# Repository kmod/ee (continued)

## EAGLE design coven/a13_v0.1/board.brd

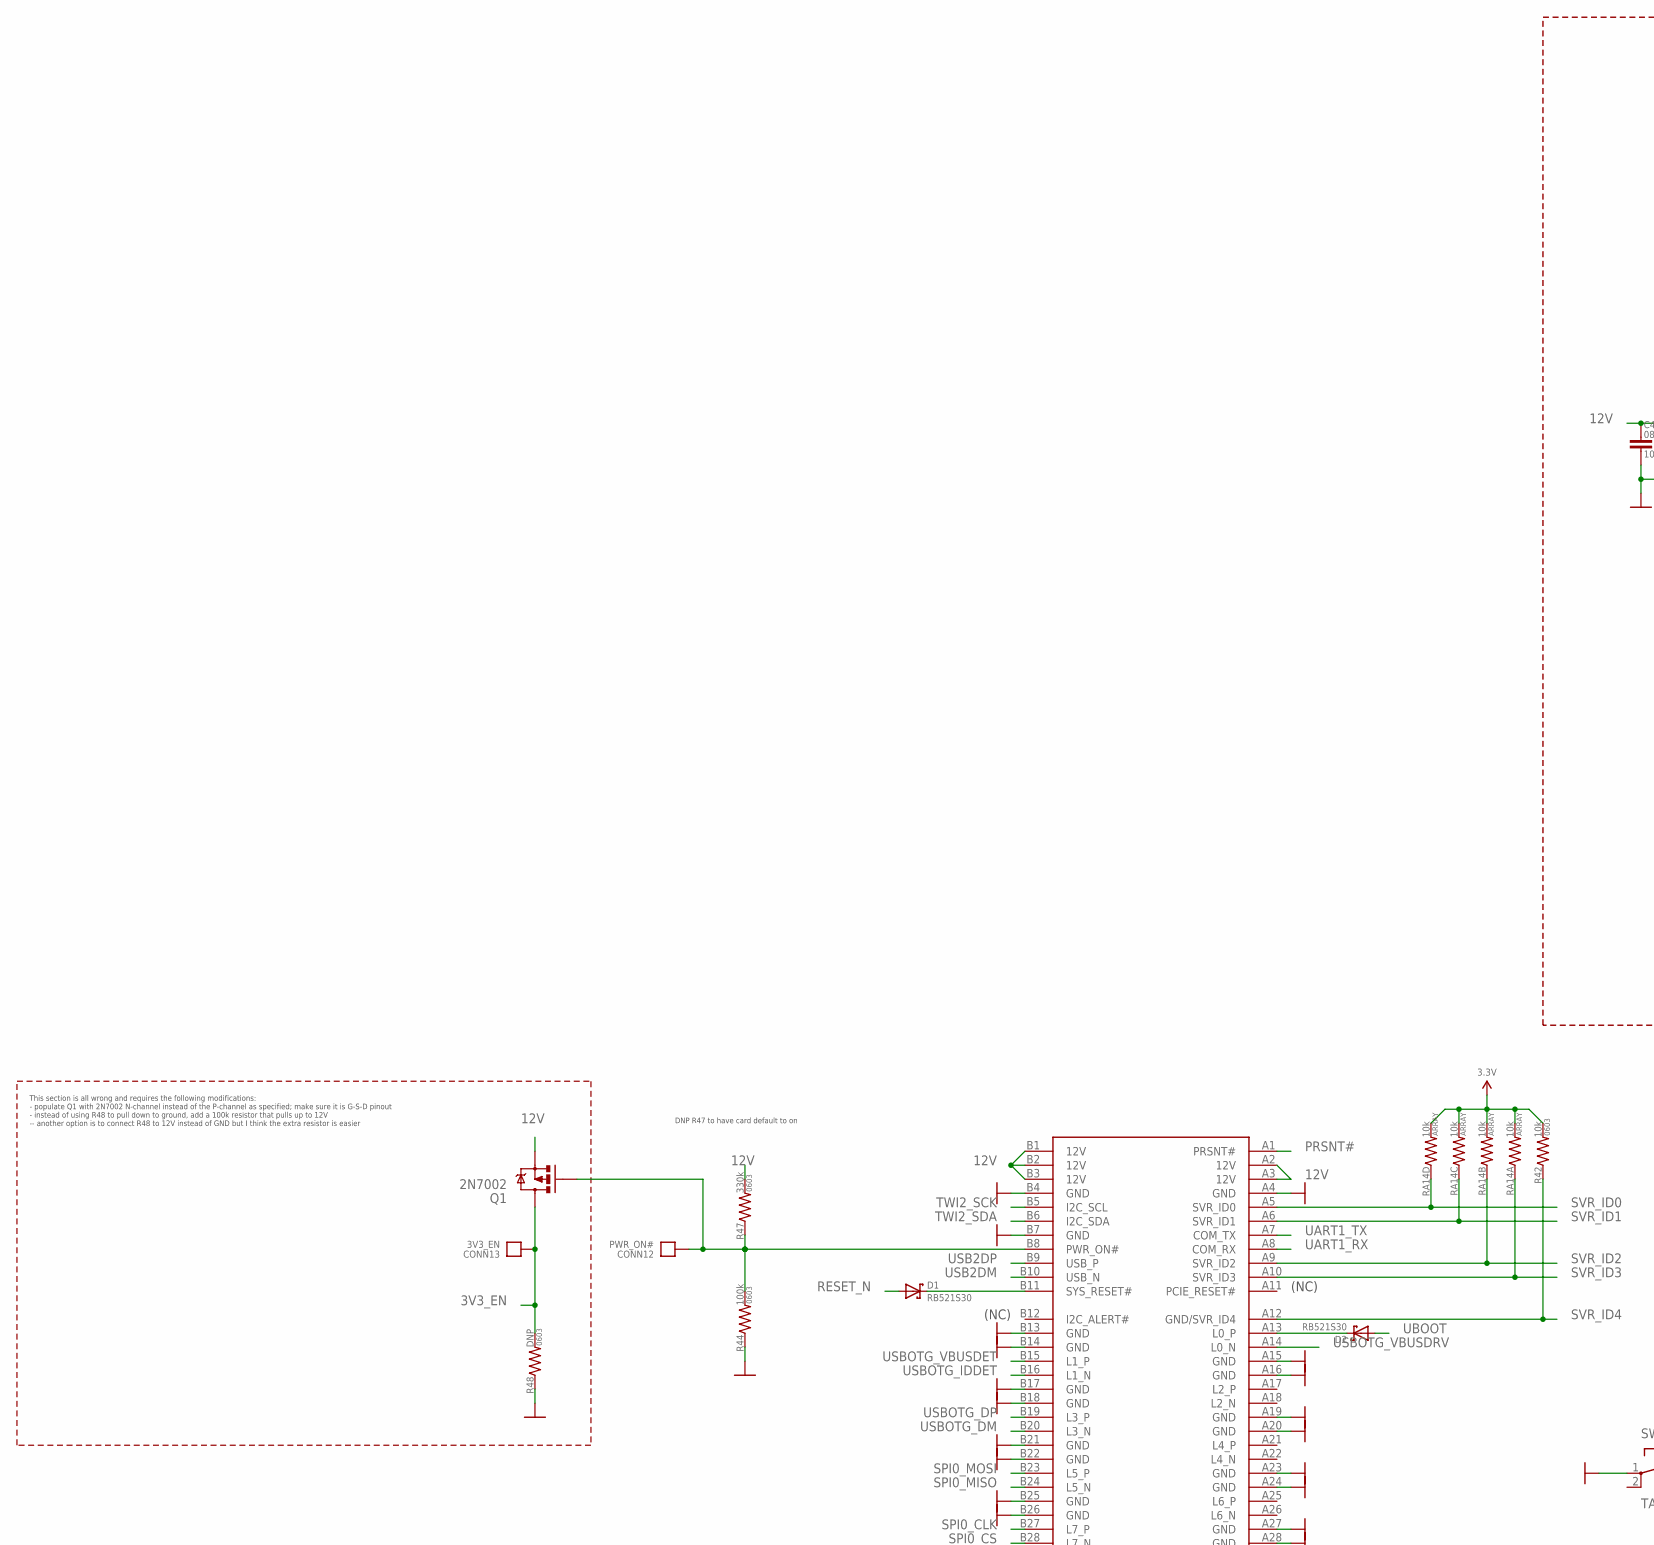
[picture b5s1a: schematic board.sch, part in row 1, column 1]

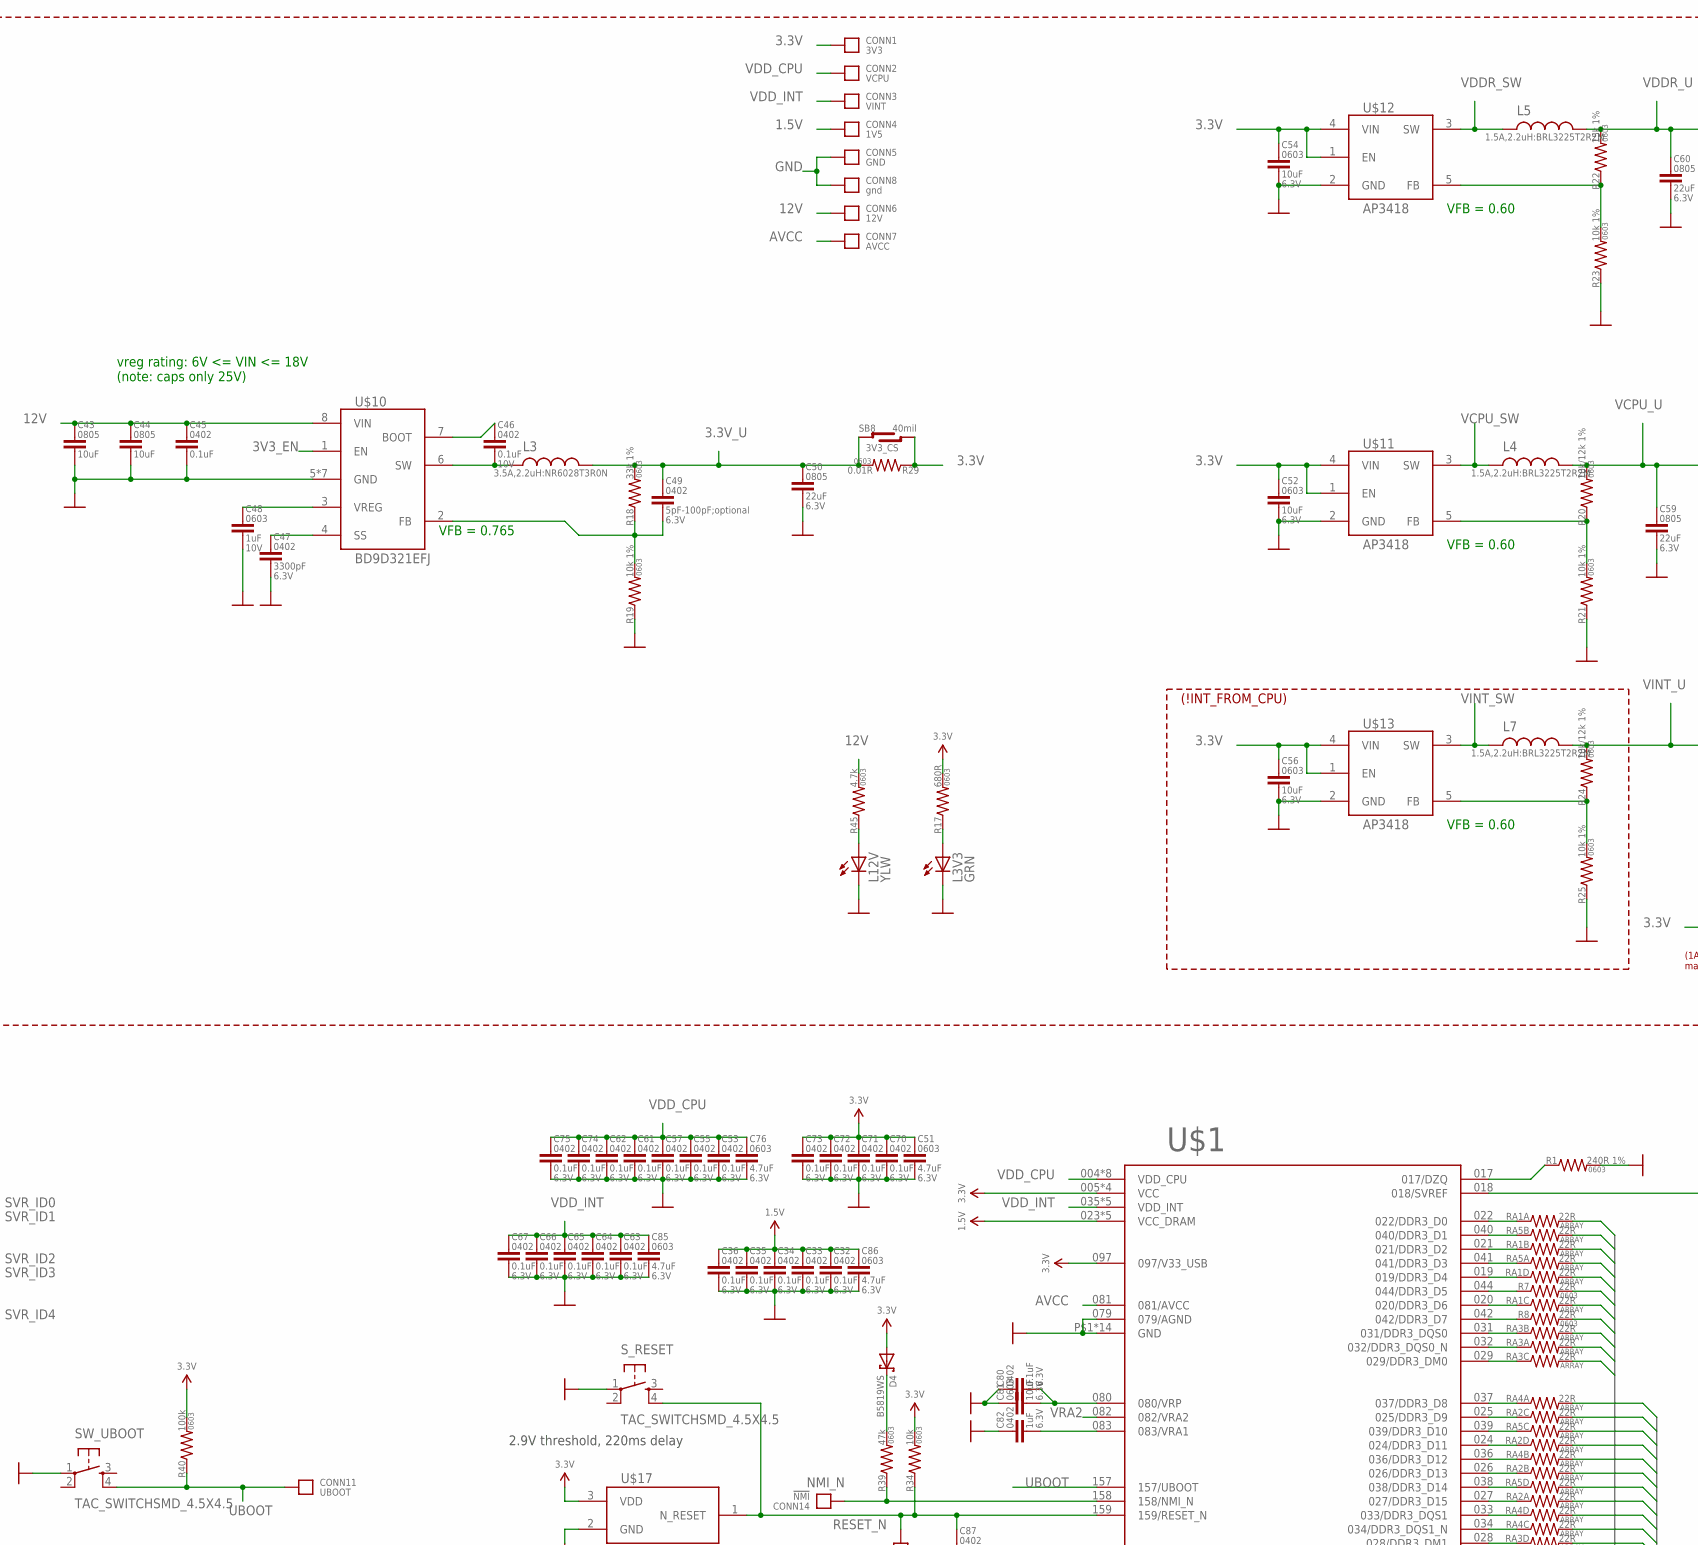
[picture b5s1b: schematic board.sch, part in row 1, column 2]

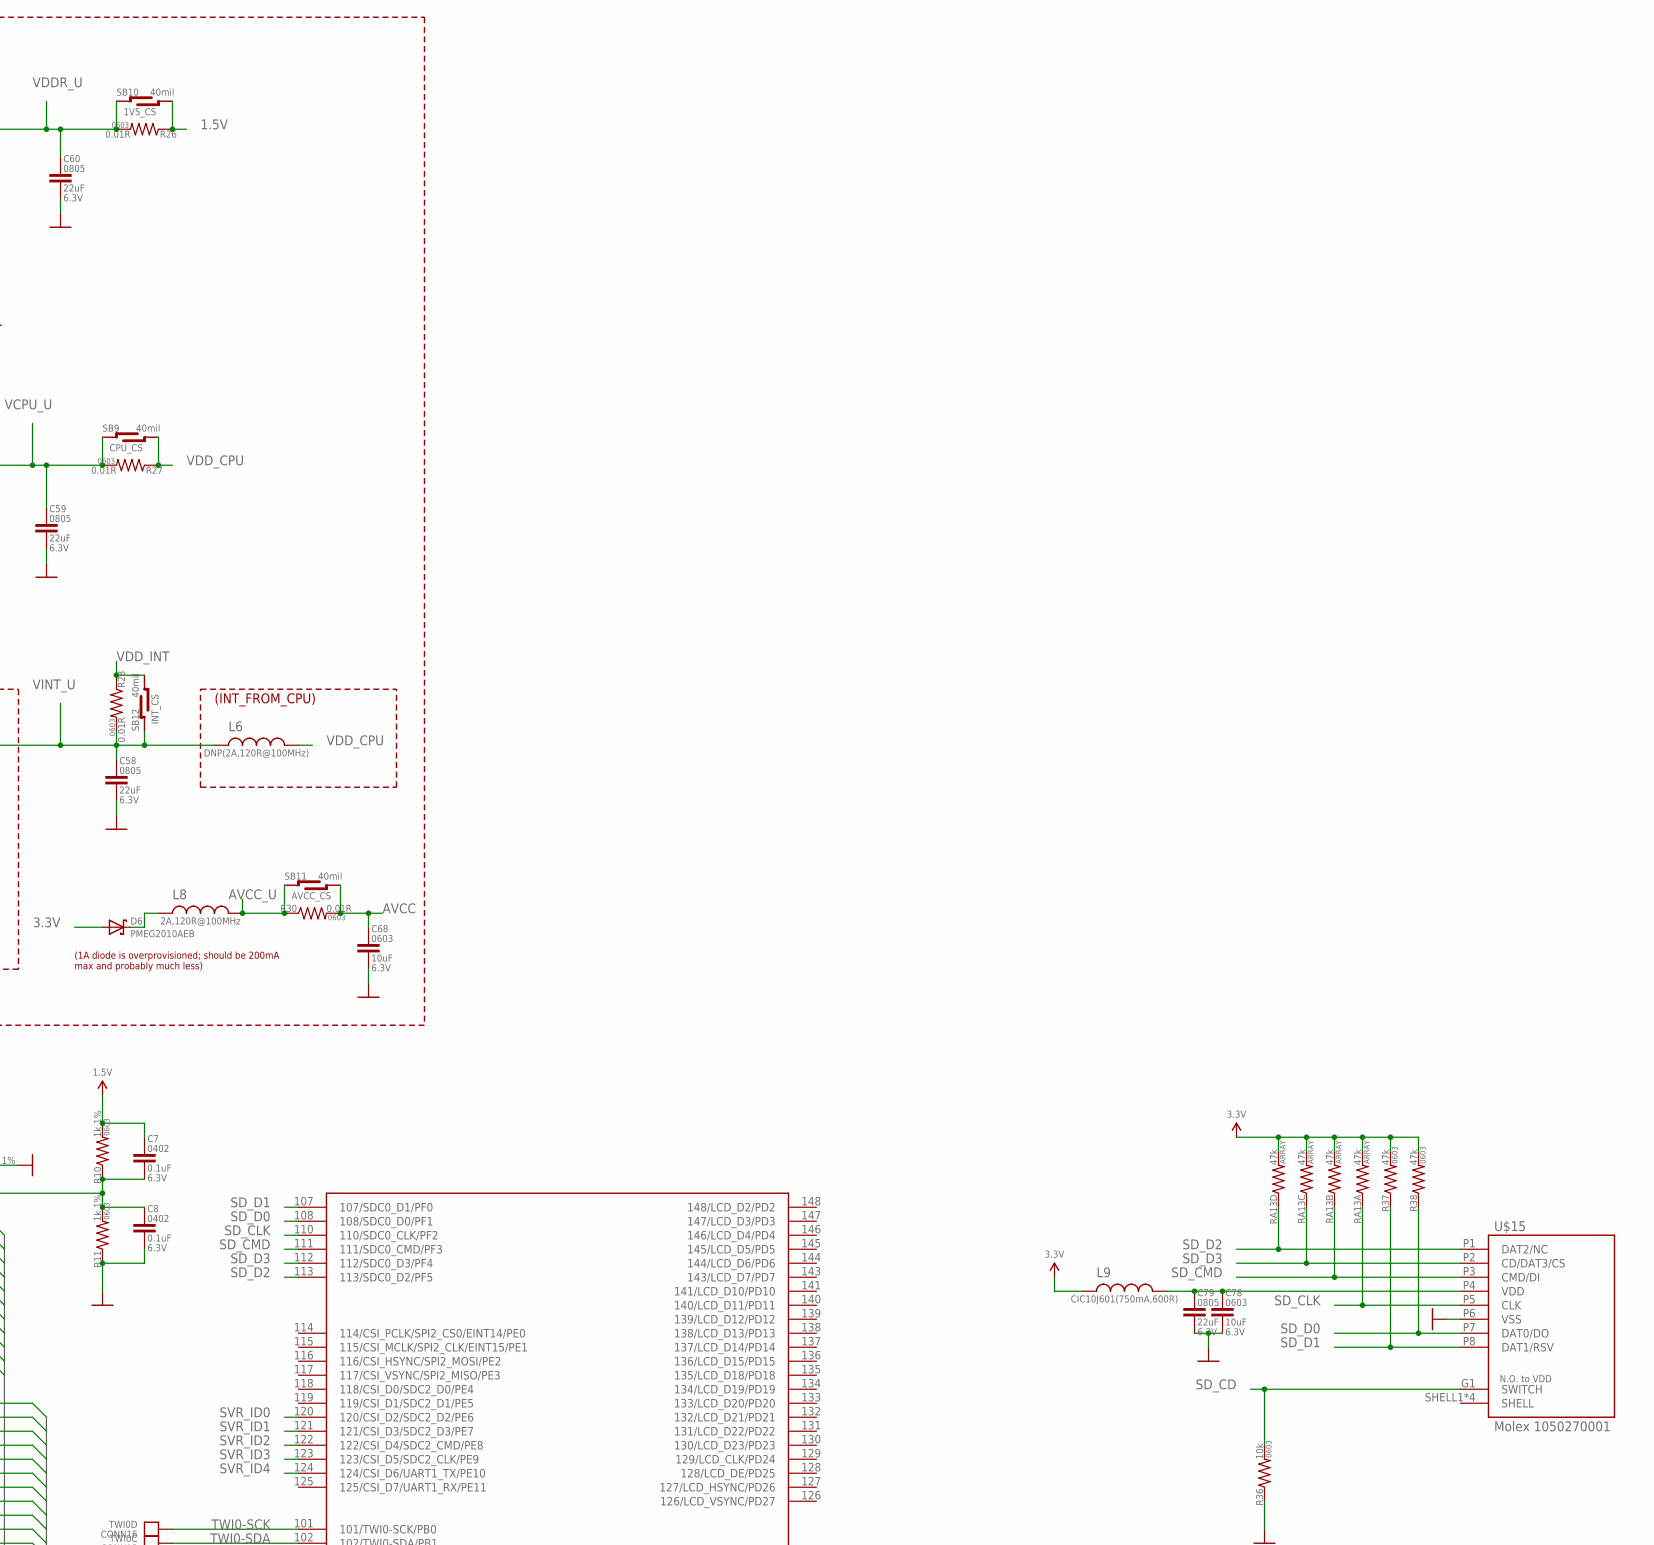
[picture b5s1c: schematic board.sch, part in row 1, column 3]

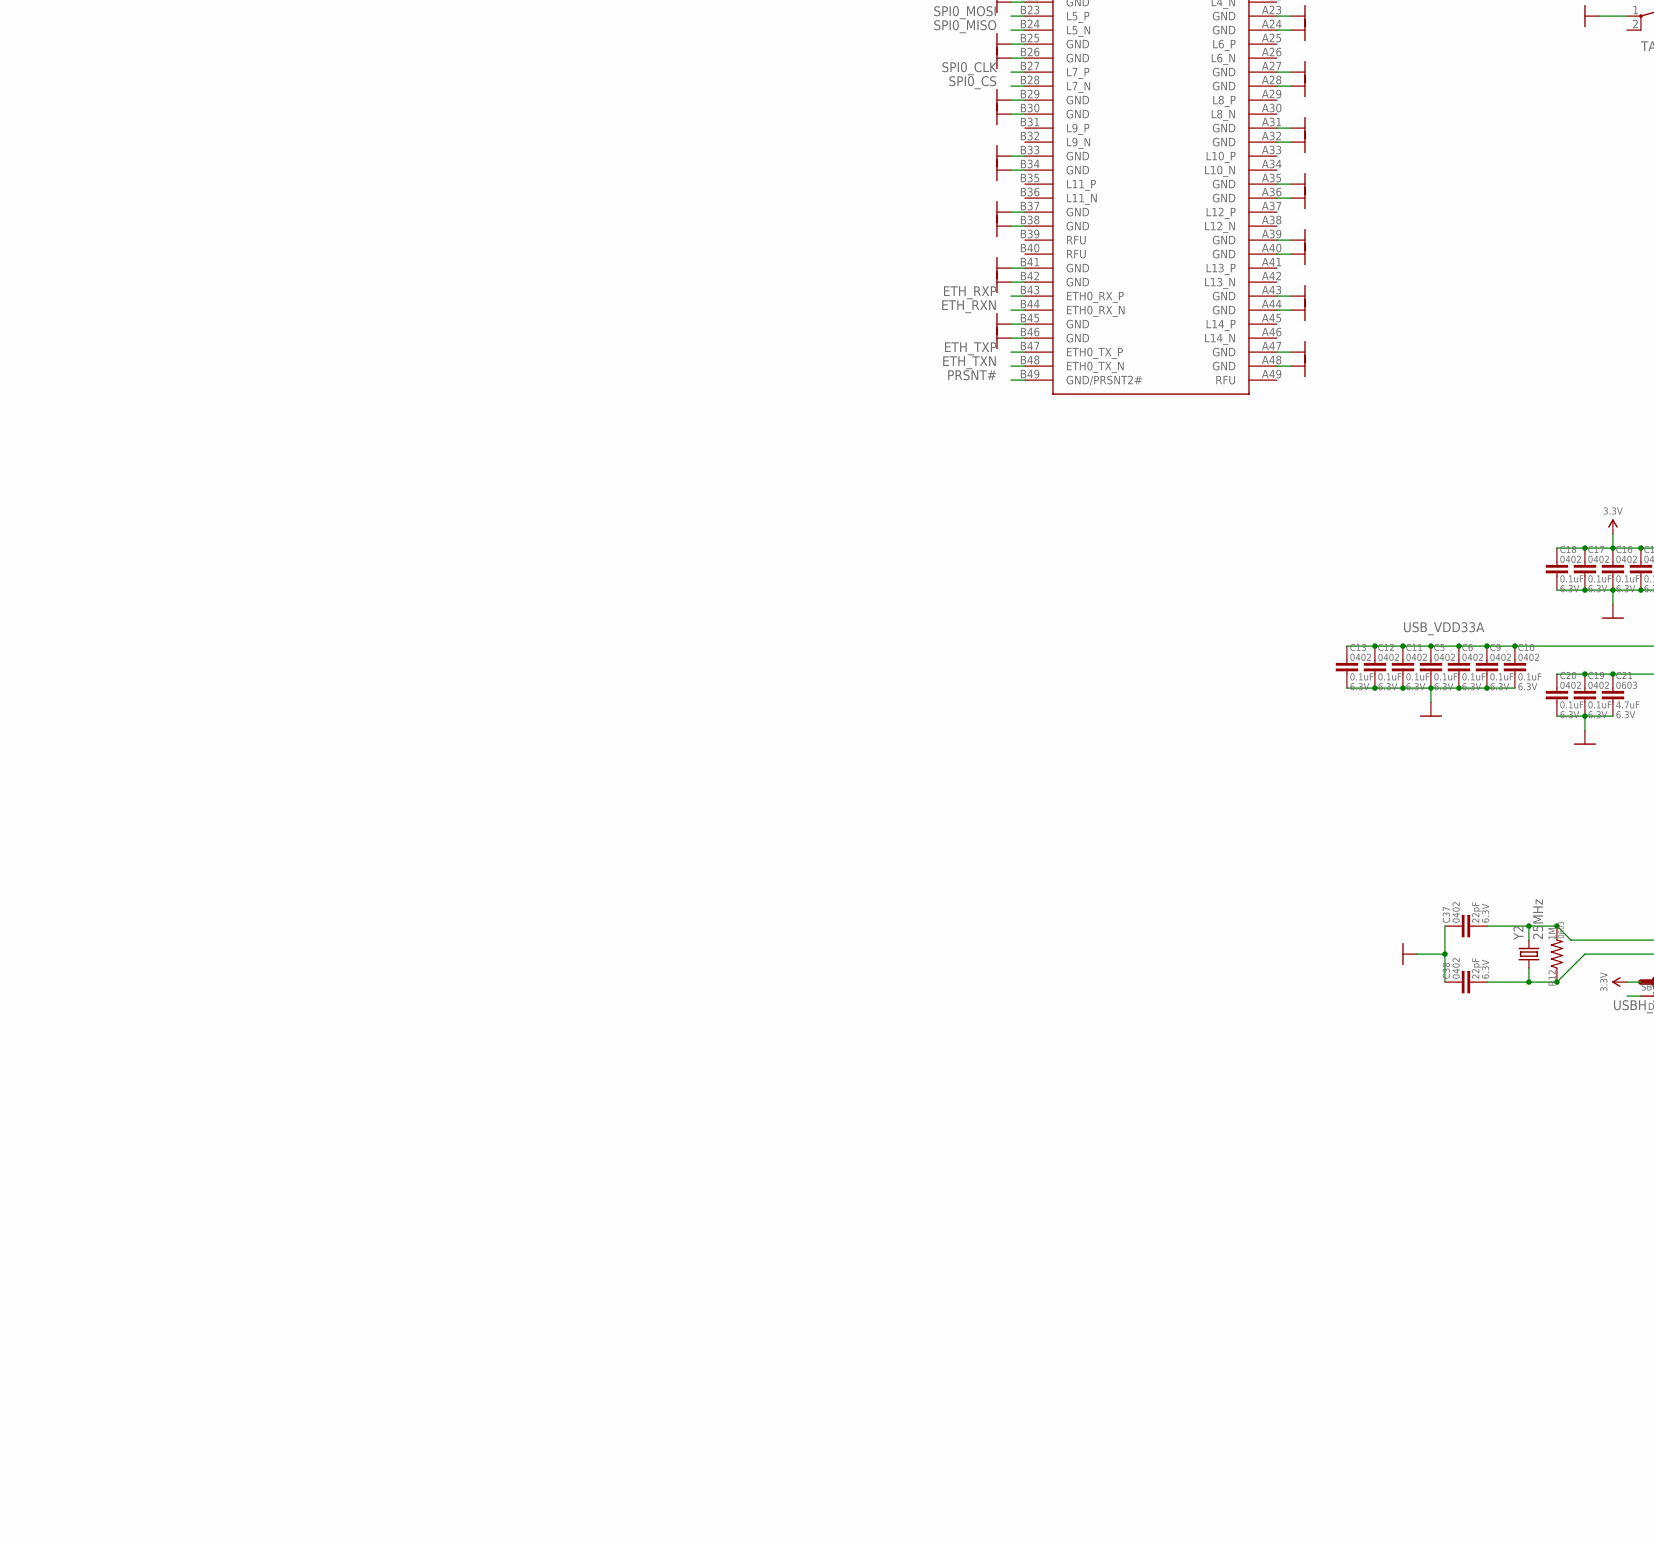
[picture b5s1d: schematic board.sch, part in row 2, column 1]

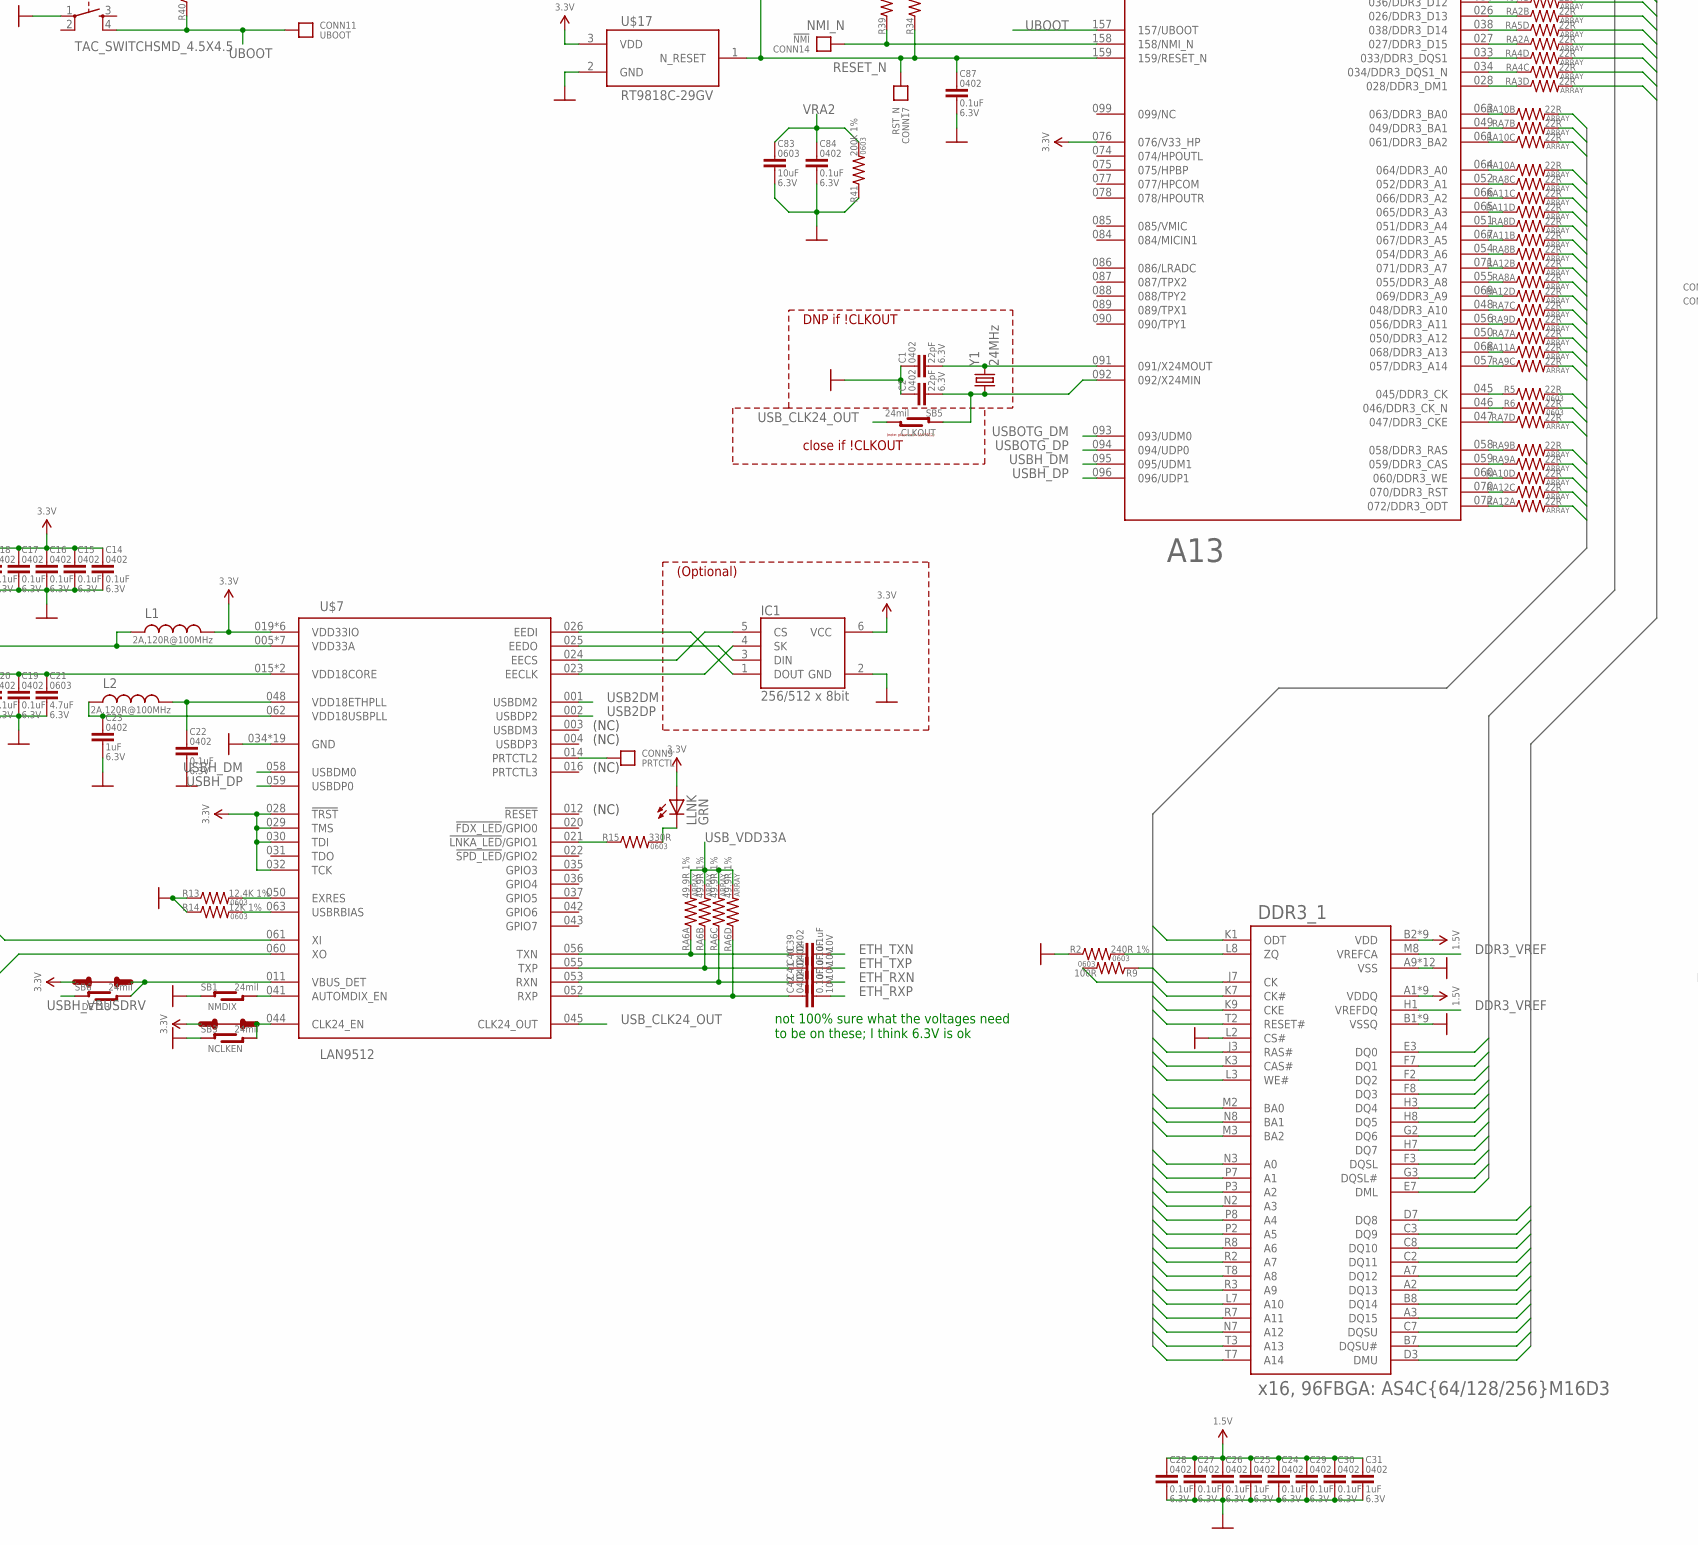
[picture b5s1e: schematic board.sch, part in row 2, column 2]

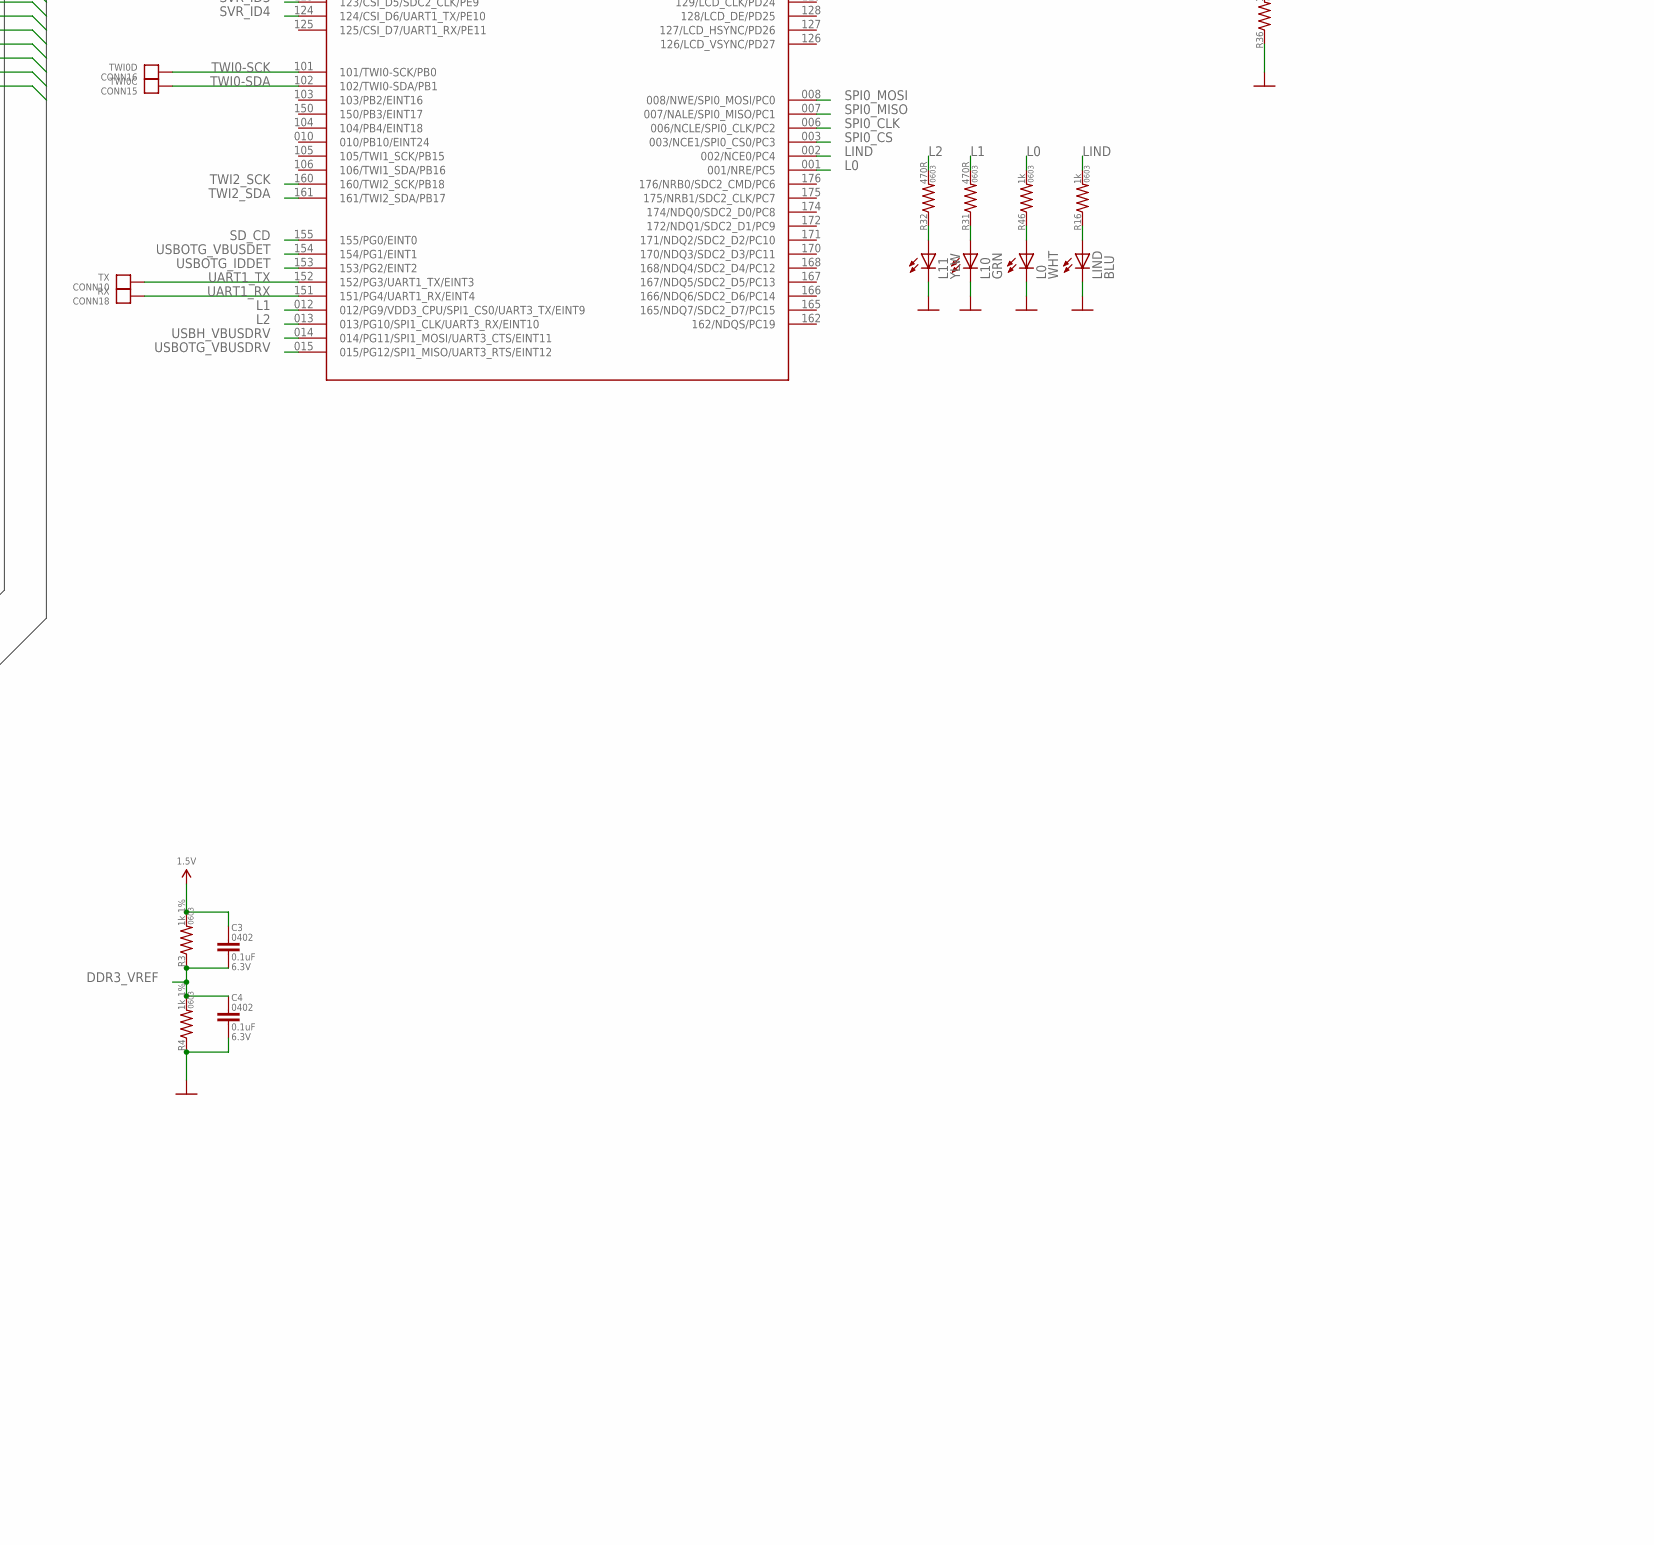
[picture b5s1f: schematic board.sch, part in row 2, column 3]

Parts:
C1, C2, C37, C38: 22pF; 0402-CAP
C3, C4, C5, C6, C7, C8, C9, C10, C11, C12, C13, C14, C15, C16, C17, C18, C19, C20, C22, C24, C26, C27, C28, C29, C30, C32, C33, C34, C35, C36, C53, C55, C57, C61, C62, C63, C64, C65, C66, C67, C70, C71, C72, C73, C74, C75, C80, C84, C87: 0.1uF; 0402-CAP
C21, C51, C76, C85, C86: 4.7uF; 0603-CAP
C23, C25, C31, C82: 1uF; 0402-CAP
C39, C40, C41, C42, C46: 0.1uF; 0402-CAP; VOLTAGE 10V
C43, C44: 10uF; 0805-CAP; VOLTAGE 25V
C45: 0.1uF; 0402-CAP; VOLTAGE 25V
C47: 3300pF; 0402-CAP
C48: 1uF; 0603-CAP; VOLTAGE 10V
C49: 5pF-100pF;optional; 0402-CAP
C50, C58, C59, C60, C79: 22uF; 0805-CAP
C52, C54, C56, C68, C78, C81, C83: 10uF; 0603-CAP
CONN1: 3V3; HOLE_22AWG
CONN2: VCPU; HOLE_22AWG
CONN3: VINT; HOLE_22AWG
CONN4: 1V5; HOLE_22AWG
CONN5: GND; HOLE_22AWG
CONN6: 12V; HOLE_22AWG
CONN7: AVCC; HOLE_22AWG
CONN8: gnd; CLIP-AREA
CONN9: PRTCTL; HOLE_22AWG
CONN10: TX; HOLE_22AWG
CONN11: UBOOT; HOLE_22AWG
CONN12: PWR_ON#; TESTPAD-1.27
CONN13: 3V3_EN; TESTPAD-2MM
CONN14: !NMI; HOLE_22AWG
CONN15: TWI0C; TESTPAD-1.27
CONN16: TWI0D; TESTPAD-1.27
CONN17: RST_N; HOLE_22AWG
CONN18: RX; HOLE_22AWG
D1, D2: RB521S30; SOD-523
D4: B5819WS; SOD-323
D6: PMEG2010AEB; SOD-523
DDR3_1: x16, 96FBGA: AS4C{64/128/256}M16D3; BGA96
IC1: 256/512 x 8bit; SOT23-6L
L0: WHT; 0603_LED
L1, L2, L8: 2A,120R@100MHz; 0603
L3: 3.5A,2.2uH:NR6028T3R0N; NR60XX
L3V3, L10: GRN; 0603_LED
L4, L5, L7: 1.5A,2.2uH:BRL3225T2R2M; 1206
L6: DNP(2A,120R@100MHz); 0603
L9: CIC10J601(750mA,600R); 0603
L11, L12V: YLW; 0603_LED
LIND: BLU; 0603_LED
LLNK: GRN; 0603_LED
Q1: 2N7002; SOT23-3
R1, R2: 240R 1%; 0603-RES
R3, R4, R10, R11: 1k 1%; 0603-RES
R5, R6, R7, R8: 22R; 0603-RES
R9: 100R; 0603-RES
R12: 1M; 0603-RES
R13: 12.4K 1%; 0603-RES
R14: 12K 1%; 0603-RES
R15: 330R; 0603-RES
R16, R46: 1k; 0603-RES
R17: 680R; 0603-RES
R18: 33k 1%; 0603-RES
R19, R21, R23, R25: 10k 1%; 0603-RES
R20, R24: 10k/12k 1%; 0603-RES
R22: 15k 1%; 0603-RES
R26, R27, R28, R29, R30: 0.01R; 0603-RES
R31, R32: 470R; 0603-RES
R34, R36, R42: 10k; 0603-RES
R37, R38, R39: 47k; 0603-RES
R40, R44: 100k; 0603-RES
R41: 200k 1%; 0603-RES
R45: 4.7k; 0603-RES
R47: 330k; 0603-RES
R48: DNP; 0603-RES
RA1, RA2, RA3, RA4, RA5, RA7, RA8, RA9, RA10, RA11, RA12: 22R; 0603-ARV
RA6: 49.9R 1%; 0603-ARV
RA13: 47k; 0603-ARV
RA14: 10k; 0603-ARV
SB1: NMDIX; SOLDER-BRIDGE-OPEN
SB3: NCLKEN; SOLDER-BRIDGE-OPEN
SB4: CLKEN; TRACE-CUT
SB5: CLKOUT; SOLDER-BRIDGE-OPEN
SB6: DET13; SOLDER-BRIDGE-OPEN
SB7: DET3; TRACE-CUT
SB8: 3V3_CS; SOLDER-BRIDGE-OPEN-LARGE
SB9: CPU_CS; SOLDER-BRIDGE-OPEN-LARGE
SB10: 1V5_CS; SOLDER-BRIDGE-OPEN-LARGE
SB11: AVCC_CS; SOLDER-BRIDGE-OPEN-LARGE
SB12: INT_CS; SOLDER-BRIDGE-OPEN-LARGE
SW_UBOOT: TAC_SWITCHSMD_4.5X4.5; TAC_SWITCH_SMD_4.5X4.5
S_RESET: TAC_SWITCHSMD_4.5X4.5; TAC_SWITCH_SMD_4.5X4.5
U$1: A13; TQFP176_0.4
U$7: LAN9512; QFN64
U$10: BD9D321EFJ; HTSOP8
U$11, U$12, U$13: AP3418; SOT23-5
U$15: Molex 1050270001; MICROSD-MOLEX-1050270001
U$16: CVN-V1EDGE; CVN-V1-EDGE
U$17: RT9818C-29GV; SOT23-3
Y1: 24MHz; HC49US
Y2: 25MHz; HC49US

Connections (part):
1.5V: C3.1, C7.1, C24.1, C25.1, C26.1, C27.1, C28.1, C29.1, C30.1, C31.1, C32.1, C33.1, C34.1, C35.1, C36.1, C86.1, CONN4.P, DDR3_1.A1 (VDDQ), DDR3_1.A8 (VDDQ), DDR3_1.B2 (VDD), DDR3_1.C1 (VDDQ), DDR3_1.C9 (VDDQ), DDR3_1.D2 (VDDQ), DDR3_1.D9 (VDD), DDR3_1.E9 (VDDQ), DDR3_1.F1 (VDDQ), DDR3_1.G7 (VDD), DDR3_1.H2 (VDDQ), DDR3_1.H9 (VDDQ), DDR3_1.K2 (VDD), DDR3_1.K8 (VDD), DDR3_1.N1 (VDD), DDR3_1.N9 (VDD), DDR3_1.R1 (VDD), DDR3_1.R9 (VDD), R3.2, R10.2, R26.1, SB10.R1, SB10.R2, U$1.023 (VCC_DRAM), U$1.030 (VCC_DRAM), U$1.043 (VCC_DRAM), U$1.053 (VCC_DRAM), U$1.062 (VCC_DRAM)
3.3V: C14.1, C15.1, C16.1, C17.1, C18.1, C51.1, C52.1, C54.1, C56.1, C70.1, C71.1, C72.1, C73.1, CONN1.P, D4.A, D6.A, IC1.6 (VCC), L1.2, L9.1, LLNK.A, R17.2, R29.1, R34.2, R37.2, R38.2, R40.2, R42.2, RA13.5 (2), RA13.6 (2), RA13.7 (2), RA13.8 (2), RA14.5 (2), RA14.6 (2), RA14.7 (2), RA14.8 (2), SB4.L1, SB7.L1, SB8.R1, SB8.R2, U$1.005 (VCC), U$1.076 (076/V33_HP), U$1.097 (097/V33_USB), U$1.100 (VCC), U$1.142 (VCC), U$1.163 (VCC), U$7.019 (VDD33IO), U$7.027 (VDD33IO), U$7.028 (!TRST), U$7.029 (TMS), U$7.030 (TDI), U$7.032 (TCK), U$7.033 (VDD33IO), U$7.039 (VDD33IO), U$7.040 (VDD33IO), U$7.046 (VDD33IO), U$11.1 (EN), U$11.4 (VIN), U$12.1 (EN), U$12.4 (VIN), U$13.1 (EN), U$13.4 (VIN), U$17.3 (VDD)
3.3V_FB: C49.2, R18.1, R19.2, U$10.2 (FB)
3.3V_U: C49.1, C50.1, L3.P$2 (2), R18.2, R29.2, SB8.L1, SB8.L2
3V3_EN: CONN13.P, Q1.3 (D), R48.2, U$10.1 (EN)
12V: C43.1, C44.1, C45.1, CONN6.P, Q1.2 (S), R45.2, R47.2, U$10.8 (VIN), U$16.A2 (12V), U$16.A3 (12V), U$16.B1 (12V), U$16.B2 (12V), U$16.B3 (12V)
AVCC: C68.1, CONN7.P, R30.2, SB11.R1, SB11.R2, U$1.081 (081/AVCC)
AVCC_U: L8.2, R30.1, SB11.L1, SB11.L2
DDR3_A0: DDR3_1.N3 (A0), RA10.8 (2)
DDR3_A1: DDR3_1.P7 (A1), RA8.6 (2)
DDR3_A2: DDR3_1.P3 (A2), RA11.6 (2)
DDR3_A3: DDR3_1.N2 (A3), RA11.5 (2)
DDR3_A4: DDR3_1.P8 (A4), RA8.5 (2)
DDR3_A5: DDR3_1.P2 (A5), RA11.7 (2)
DDR3_A6: DDR3_1.R8 (A6), RA8.7 (2)
DDR3_A7: DDR3_1.R2 (A7), RA12.7 (2)
DDR3_A8: DDR3_1.T8 (A8), RA8.8 (2)
DDR3_A9: DDR3_1.R3 (A9), RA12.5 (2)
DDR3_A10: DDR3_1.L7 (A10), RA7.6 (2)
DDR3_A11: DDR3_1.R7 (A11), RA9.5 (2)
DDR3_A12: DDR3_1.N7 (A12), RA7.8 (2)
DDR3_A13: DDR3_1.T3 (A13), RA11.8 (2)
DDR3_A14: DDR3_1.T7 (A14), RA9.6 (2)
DDR3_BA0: DDR3_1.M2 (BA0), RA10.7 (2)
DDR3_BA1: DDR3_1.N8 (BA1), RA7.7 (2)
DDR3_BA2: DDR3_1.M3 (BA2), RA10.6 (2)
DDR3_CAS: DDR3_1.K3 (CAS#), RA9.8 (2)
DDR3_CK: DDR3_1.J7 (CK), R5.2, R9.1
DDR3_CK#: DDR3_1.K7 (CK#), R6.2, R9.2
DDR3_CKE: DDR3_1.K9 (CKE), RA7.5 (2)
DDR3_DML: DDR3_1.E7 (DML), RA3.6 (2)
DDR3_DMU: DDR3_1.D3 (DMU), RA3.5 (2)
DDR3_DQ0: DDR3_1.E3 (DQ0), RA1.8 (2)
DDR3_DQ1: DDR3_1.F7 (DQ1), RA5.7 (2)
DDR3_DQ2: DDR3_1.F2 (DQ2), RA1.7 (2)
DDR3_DQ3: DDR3_1.F8 (DQ3), RA5.8 (2)
DDR3_DQ4: DDR3_1.H3 (DQ4), RA1.5 (2)
DDR3_DQ5: DDR3_1.H8 (DQ5), R7.2
DDR3_DQ6: DDR3_1.G2 (DQ6), RA1.6 (2)
DDR3_DQ7: DDR3_1.H7 (DQ7), R8.2
DDR3_DQ8: DDR3_1.D7 (DQ8), RA4.8 (2)
DDR3_DQ9: DDR3_1.C3 (DQ9), RA2.6 (2)
DDR3_DQ10: DDR3_1.C8 (DQ10), RA5.6 (2)
DDR3_DQ11: DDR3_1.C2 (DQ11), RA2.5 (2)
DDR3_DQ12: DDR3_1.A7 (DQ12), RA4.7 (2)
DDR3_DQ13: DDR3_1.A2 (DQ13), RA2.7 (2)
DDR3_DQ14: DDR3_1.B8 (DQ14), RA5.5 (2)
DDR3_DQ15: DDR3_1.A3 (DQ15), RA2.8 (2)
DDR3_DQSL: DDR3_1.F3 (DQSL), RA3.7 (2)
DDR3_DQSL#: DDR3_1.G3 (DQSL#), RA3.8 (2)
DDR3_DQSU: DDR3_1.C7 (DQSU), RA4.5 (2)
DDR3_DQSU#: DDR3_1.B7 (DQSU#), RA4.6 (2)
DDR3_ODT: DDR3_1.K1 (ODT), RA12.8 (2)
DDR3_RAS: DDR3_1.J3 (RAS#), RA9.7 (2)
DDR3_RST: DDR3_1.T2 (RESET#), RA12.6 (2)
DDR3_VREF: C3.2, C4.1, DDR3_1.H1 (VREFDQ), DDR3_1.M8 (VREFCA), R3.1, R4.2
DDR3_WE: DDR3_1.L3 (WE#), RA10.5 (2)
ETH_RXN: C41.2, U$16.B44 (ETH0_RX_N)
ETH_RXP: C42.2, U$16.B43 (ETH0_RX_P)
ETH_TXN: C39.2, U$16.B48 (ETH0_TX_N)
ETH_TXP: C40.2, U$16.B47 (ETH0_TX_P)
GND: C1.1, C2.1, C4.2, C5.2, C6.2, C8.2, C9.2, C10.2, C11.2, C12.2, C13.2, C14.2, C15.2, C16.2, C17.2, C18.2, C19.2, C20.2, C21.2, C22.2, C23.2, C24.2, C25.2, C26.2, C27.2, C28.2, C29.2, C30.2, C31.2, C32.2, C33.2, C34.2, C35.2, C36.2, C37.1, C38.1, C43.2, C44.2, C45.2, C47.2, C48.2, C50.2, C51.2, C52.2, C53.2, C54.2, C55.2, C56.2, C57.2, C58.2, C59.2, C60.2, C61.2, C62.2, C63.2, C64.2, C65.2, C66.2, C67.2, C68.2, C70.2, C71.2, C72.2, C73.2, C74.2, C75.2, C76.2, C78.2, C79.2, C80.1, C81.1, C82.1, C83.2, C84.2, C85.2, C86.2, C87.2, CONN5.P, CONN8.P$1, CONN8.P$2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
L0: R46.2, U$1.001 (001/NRE/PC5)
L1: R31.2, U$1.012 (012/PG9/VDD3_CPU/SPI1_CS0/UART3_TX/EINT9)
L2: R32.2, U$1.013 (013/PG10/SPI1_CLK/UART3_RX/EINT10)
LAN_VBUSDET: SB6.R1, SB6.R2, SB7.R1, U$7.011 (VBUS_DET)
LIND: R16.2, U$1.002 (002/NCE0/PC4)
unnamed: R1.1, U$1.017 (017/DZQ)
unnamed: RA1.3 (1), U$1.020 (020/DDR3_D6)
unnamed: C1.2, U$1.091 (091/X24MOUT), Y1.2
unnamed: C2.2, SB5.L1, SB5.L2, U$1.092 (092/X24MIN), Y1.1
unnamed: RA1.4 (1), U$1.019 (019/DDR3_D4)
unnamed: DDR3_1.L8 (ZQ), R2.2
unnamed: RA3.4 (1), U$1.028 (028/DDR3_DM1)
unnamed: RA4.3 (1), U$1.034 (034/DDR3_DQS1_N)
unnamed: RA4.4 (1), U$1.033 (033/DDR3_DQS1)
unnamed: RA2.1, U$1.027 (027/DDR3_D15)
unnamed: RA5.4 (1), U$1.038 (038/DDR3_D14)
unnamed: RA2.2 (1), U$1.026 (026/DDR3_D13)
unnamed: RA4.2 (1), U$1.036 (036/DDR3_D12)
unnamed: RA2.4 (1), U$1.024 (024/DDR3_D11)
unnamed: RA5.3 (1), U$1.039 (039/DDR3_D10)
unnamed: RA2.3 (1), U$1.025 (025/DDR3_D9)
unnamed: RA4.1, U$1.037 (037/DDR3_D8)
unnamed: RA3.3 (1), U$1.029 (029/DDR3_DM0)
unnamed: RA3.1, U$1.032 (032/DDR3_DQS0_N)
unnamed: RA3.2 (1), U$1.031 (031/DDR3_DQS0)
unnamed: R8.1, U$1.042 (042/DDR3_D7)
unnamed: R7.1, U$1.044 (044/DDR3_D5)
unnamed: RA5.1, U$1.041 (041/DDR3_D3)
unnamed: RA1.2 (1), U$1.021 (021/DDR3_D2)
unnamed: RA5.2 (1), U$1.040 (040/DDR3_D1)
unnamed: RA1.1, U$1.022 (022/DDR3_D0)
unnamed: RA10.2 (1), U$1.063 (063/DDR3_BA0)
unnamed: RA7.2 (1), U$1.049 (049/DDR3_BA1)
unnamed: RA10.3 (1), U$1.061 (061/DDR3_BA2)
unnamed: RA10.1, U$1.064 (064/DDR3_A0)
unnamed: RA8.3 (1), U$1.052 (052/DDR3_A1)
unnamed: RA11.3 (1), U$1.066 (066/DDR3_A2)
unnamed: RA11.4 (1), U$1.065 (065/DDR3_A3)
unnamed: RA8.4 (1), U$1.051 (051/DDR3_A4)
unnamed: RA11.2 (1), U$1.067 (067/DDR3_A5)
unnamed: RA8.2 (1), U$1.054 (054/DDR3_A6)
unnamed: RA12.2 (1), U$1.071 (071/DDR3_A7)
unnamed: RA8.1, U$1.055 (055/DDR3_A8)
unnamed: RA12.4 (1), U$1.069 (069/DDR3_A9)
unnamed: RA7.3 (1), U$1.048 (048/DDR3_A10)
unnamed: RA9.4 (1), U$1.056 (056/DDR3_A11)
unnamed: RA7.1, U$1.050 (050/DDR3_A12)
unnamed: RA11.1, U$1.068 (068/DDR3_A13)
unnamed: RA9.3 (1), U$1.057 (057/DDR3_A14)
unnamed: R5.1, U$1.045 (045/DDR3_CK)
unnamed: R6.1, U$1.046 (046/DDR3_CK_N)
unnamed: RA7.4 (1), U$1.047 (047/DDR3_CKE)
unnamed: RA9.2 (1), U$1.058 (058/DDR3_RAS)
unnamed: RA9.1, U$1.059 (059/DDR3_CAS)
unnamed: RA10.4 (1), U$1.060 (060/DDR3_WE)
unnamed: RA12.3 (1), U$1.070 (070/DDR3_RST)
unnamed: RA12.1, U$1.072 (072/DDR3_ODT)
unnamed: C22.1, L2.2, U$7.048 (VDD18ETHPLL)
unnamed: C23.1, L2.1, U$7.062 (VDD18USBPLL)
unnamed: C37.2, R12.2, U$7.061 (XI), Y2.2
unnamed: IC1.5 (CS), U$7.024 (EECS)
unnamed: C19.1, C20.1, C21.1, U$7.015 (VDD18CORE), U$7.038 (VDD18CORE)
unnamed: C38.2, R12.1, U$7.060 (XO), Y2.1
unnamed: C39.1, RA6.1, U$7.056 (TXN)
unnamed: C40.1, RA6.2 (1), U$7.055 (TXP)
unnamed: C41.1, RA6.3 (1), U$7.053 (RXN)
unnamed: C42.1, RA6.4 (1), U$7.052 (RXP)
unnamed: IC1.4 (SK), U$7.023 (EECLK)
unnamed: IC1.1 (DOUT), U$7.026 (EEDI)
unnamed: IC1.3 (DIN), U$7.025 (EEDO)
unnamed: LIND.A, R16.1
unnamed: R13.2, U$7.050 (EXRES)
unnamed: R14.2, U$7.063 (USBRBIAS)
unnamed: C46.2, L3.P$1 (1), U$10.6 (SW)
unnamed: C46.1, U$10.7 (BOOT)
unnamed: C48.1, U$10.3 (VREG)
unnamed: SB1.R1, SB1.R2, U$7.041 (AUTOMDIX_EN)
unnamed: R15.1, U$7.021 (!LNKA_LED!/GPIO1)
unnamed: LLNK.C, R15.2
unnamed: C47.1, U$10.4 (SS)
unnamed: SB3.R1, SB3.R2, SB4.R1, U$7.044 (CLK24_EN)
unnamed: CONN9.P, U$7.014 (PRTCTL2)
unnamed: L10.A, R31.1
unnamed: L3V3.A, R17.1
unnamed: R20.1, R21.2, U$11.5 (FB)
unnamed: L12V.A, R45.1
unnamed: R22.1, R23.2, U$12.5 (FB)
unnamed: L11.A, R32.1
unnamed: R24.1, R25.2, U$13.5 (FB)
unnamed: D1.C, U$16.B11 (SYS_RESET#)
unnamed: D4.C, R39.2
unnamed: D2.C, U$16.A13 (L0_P)
unnamed: D6.C, L8.1
unnamed: C78.1, C79.1, L9.2, U$15.P4 (VDD)
unnamed: L0.A, R46.1
NMI_N: CONN14.P, R39.1, U$1.158 (158/NMI_N)
PRSNT#: U$16.A1 (PRSNT#), U$16.B49 (GND/PRSNT2#)
PWR_ON#: CONN12.P, Q1.1 (G), R44.2, R47.1, U$16.B8 (PWR_ON#)
RESET_N: C87.1, CONN17.P, D1.A, R34.1, S_RESET.4, U$1.159 (159/RESET_N), U$17.1 (N_RESET)
SD_CD: R36.2, U$1.155 (155/PG0/EINT0), U$15.G1 (SWITCH)
SD_CLK: RA13.1, U$1.110 (110/SDC0_CLK/PF2), U$15.P5 (CLK)
SD_CMD: RA13.2 (1), U$1.111 (111/SDC0_CMD/PF3), U$15.P3 (CMD/DI)
SD_D0: R38.1, U$1.108 (108/SDC0_D0/PF1), U$15.P7 (DAT0/DO)
SD_D1: R37.1, U$1.107 (107/SDC0_D1/PF0), U$15.P8 (DAT1/RSV)
SD_D2: RA13.4 (1), U$1.113 (113/SDC0_D2/PF5), U$15.P1 (DAT2/NC)
SD_D3: RA13.3 (1), U$1.112 (112/SDC0_D3/PF4), U$15.P2 (CD/DAT3/CS)
SPI0_CLK: U$1.006 (006/NCLE/SPI0_CLK/PC2), U$16.B27 (L7_P)
SPI0_CS: U$1.003 (003/NCE1/SPI0_CS0/PC3), U$16.B28 (L7_N)
SPI0_MISO: U$1.007 (007/NALE/SPI0_MISO/PC1), U$16.B24 (L5_N)
SPI0_MOSI: U$1.008 (008/NWE/SPI0_MOSI/PC0), U$16.B23 (L5_P)
SVREF: C7.2, C8.1, R10.1, R11.2, U$1.018 (018/SVREF)
SVR_ID0: RA14.4 (1), U$1.120 (120/CSI_D2/SDC2_D2/PE6), U$16.A5 (SVR_ID0)
SVR_ID1: RA14.3 (1), U$1.121 (121/CSI_D3/SDC2_D3/PE7), U$16.A6 (SVR_ID1)
SVR_ID2: RA14.2 (1), U$1.122 (122/CSI_D4/SDC2_CMD/PE8), U$16.A9 (SVR_ID2)
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
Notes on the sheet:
(NC)
(Optional)
VFB = 0.765
vreg rating: 6V <= VIN <= 18V (note: caps only 25V)
VFB = 0.60
(INT_FROM_CPU)
(\!INT_FROM_CPU)
DNP if \!CLKOUT
close if \!CLKOUT
(note: place near LAN9512)
(1A diode is overprovisioned; should be 200mA max and probably much less)
2.9V threshold, 220ms delay
not 100% sure what the voltages need to be on these; I think 6.3V is ok
DNP R47 to have card default to on
This section is all wrong and requires the following modifications: - populate Q1 with 2N7002 N-channel instead of the P-channel as specified; make sure it is G-S-D pinout - instead of using R48 to pull down to ground, add a 100k resistor that pulls up to 12V -- another option is to connect R48 to 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
